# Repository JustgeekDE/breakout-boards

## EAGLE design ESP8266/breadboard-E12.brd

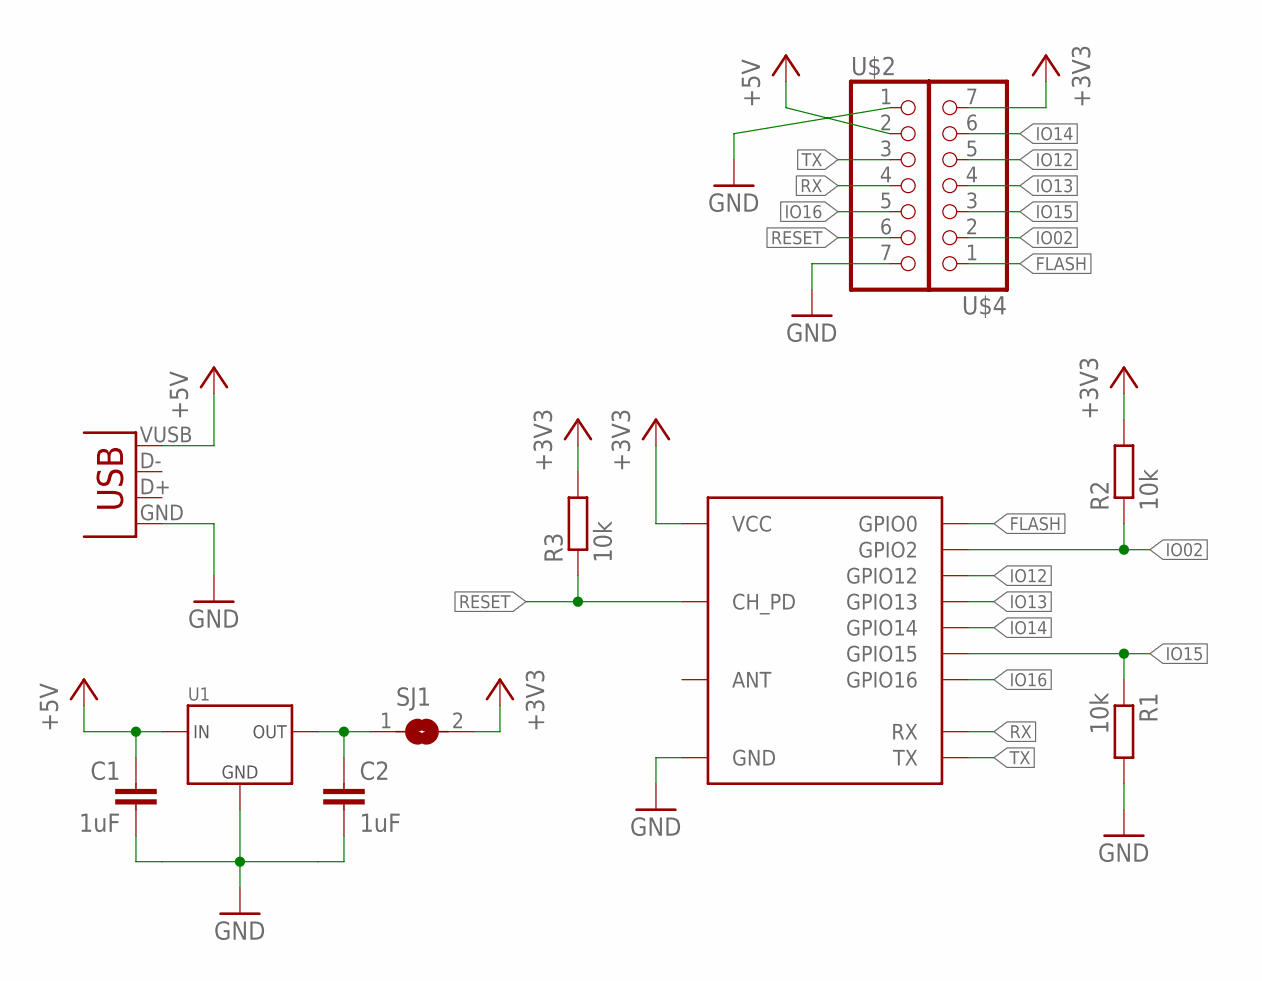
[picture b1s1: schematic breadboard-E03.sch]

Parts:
C1, C2: 1uF; C0805
CON1: USBMICRO-NO_CENTER; USB-MICRO-SMD-NO_CENTER
R1, R2, R3: 10k; R0603
SJ1: SJ
U1: REGULATOR-XC6206SOT23; SOT23
U$1: ESP8266-03; ESP8266-ESP-03
U$2, U$4: GENERIC-1X7; PINHEADER-100MIL-1X7

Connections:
+3V3: R2.2, R3.2, SJ1.2, U$1.P$8 (VCC), U$4.7
+5V: C1.1, CON1.VUSB (VBUS), U1.P$3 (IN), U$2.2
FLASH: U$1.P$14 (GPIO0), U$4.1
GND: C1.2, C2.2, CON1.GND, R1.2, U1.P$1 (GND), U$1.P$1 (GND), U$2.1, U$2.7
IO02: R2.1, U$1.P$13 (GPIO2), U$4.2
IO12: U$1.P$10 (GPIO12), U$4.5
IO13: U$1.P$11 (GPIO13), U$4.4
IO14: U$1.P$9 (GPIO14), U$4.6
IO15: R1.1, U$1.P$12 (GPIO15), U$4.3
IO16: U$1.P$5 (GPIO16), U$2.5
unnamed: C2.1, SJ1.1, U1.P$2 (OUT)
RESET: R3.1, U$1.P$6 (CH_PD), U$2.6
RX: U$1.P$4 (RX), U$2.4
TX: U$1.P$3 (TX), U$2.3

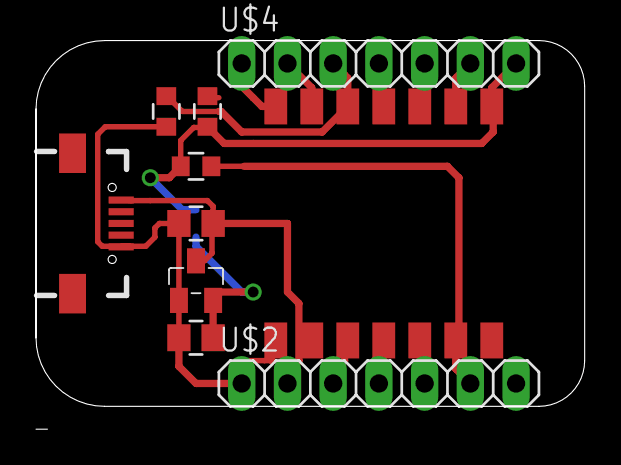
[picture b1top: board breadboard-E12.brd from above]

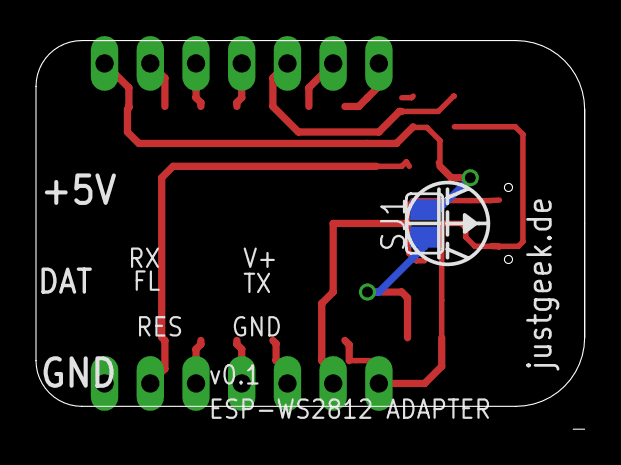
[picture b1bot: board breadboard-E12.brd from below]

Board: 2 copper layers, 30.5 x 21.6 mm, 12 parts (2 on the bottom side), 14 nets.

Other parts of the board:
U$3: LOGO-JUSTGEEK-XS

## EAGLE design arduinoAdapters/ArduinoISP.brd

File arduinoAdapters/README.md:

# Arduino ISP
A small adapter from the arduino header to the common AVR 6-pin programming header. Can be etched with basic home equipment.

Use a jumper wire to connect to the 5V rail on the other side of the Arduino, if necessary.

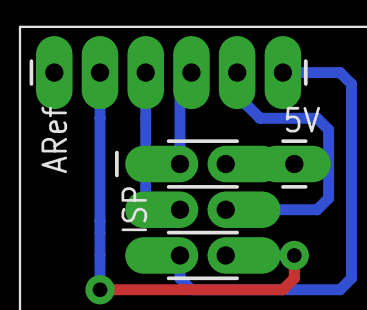
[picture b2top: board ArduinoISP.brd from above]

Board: 2 copper layers, 3 parts (0 on the bottom side), 6 nets.

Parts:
5V: M01PTH_LONGPAD; 1X01_LONGPAD
CON: 1X06_LONGPADS
ISP: AVR_SPI_PRG_6OFFSET_PADS; 2X3_OFFSET

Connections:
GND: CON.2, ISP.6
MISO: CON.4, ISP.1
MOSI: CON.5, ISP.4
RESET: CON.6, ISP.5
SCK: CON.3, ISP.3
VCC: 5V.1, ISP.2

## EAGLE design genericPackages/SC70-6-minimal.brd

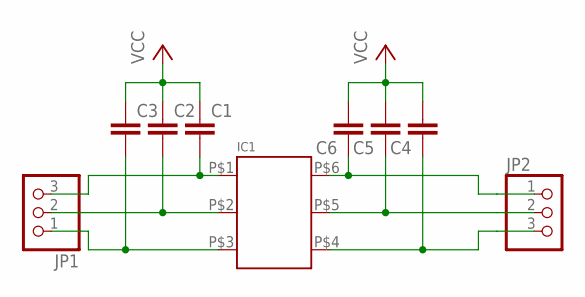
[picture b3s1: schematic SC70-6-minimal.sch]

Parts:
C1, C2, C3, C4, C5, C6: C-EUC0603; C0603
IC1: FOOTPRINT-6-PINSC70; SC-70/6
JP1, JP2: PINHD-1X3; 1X03

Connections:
1: C1.2, IC1.P$1 (1), JP1.3
2: C2.2, IC1.P$2 (2), JP1.2
3: C3.2, IC1.P$3 (3), JP1.1
4: C4.1, IC1.P$4 (4), JP2.3
5: C5.1, IC1.P$5 (5), JP2.2
6: C6.1, IC1.P$6 (6), JP2.1
VCC: C1.1, C2.1, C3.1, C4.2, C5.2, C6.2

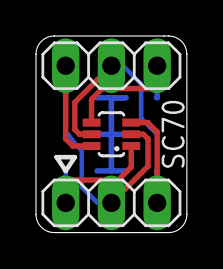
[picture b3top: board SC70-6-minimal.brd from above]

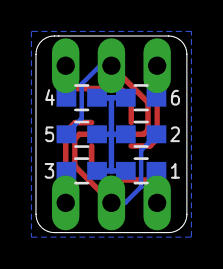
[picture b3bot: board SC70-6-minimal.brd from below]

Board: 2 copper layers, 8.4 x 10.9 mm, 9 parts (6 on the bottom side), 7 nets.

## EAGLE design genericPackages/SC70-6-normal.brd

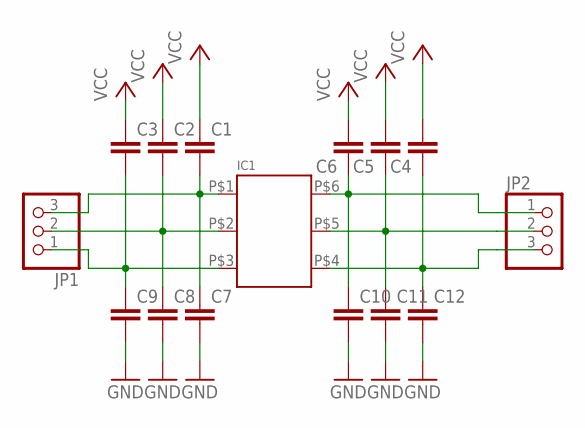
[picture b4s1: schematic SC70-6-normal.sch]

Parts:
C1, C2, C3, C4, C5, C6: C-EUC0805; C0805
C7, C8, C9, C10, C11, C12: C-EUC0603; C0603
IC1: FOOTPRINT-6-PINSC70; SC-70/6
JP1, JP2: PINHD-1X3; 1X03

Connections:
1: C1.2, C7.1, IC1.P$1 (1), JP1.3
2: C2.2, C8.1, IC1.P$2 (2), JP1.2
3: C3.2, C9.1, IC1.P$3 (3), JP1.1
4: C4.1, C12.1, IC1.P$4 (4), JP2.3
5: C5.1, C11.1, IC1.P$5 (5), JP2.2
6: C6.1, C10.1, IC1.P$6 (6), JP2.1
GND: C7.2, C8.2, C9.2, C10.2, C11.2, C12.2
VCC: C1.1, C2.1, C3.1, C4.2, C5.2, C6.2

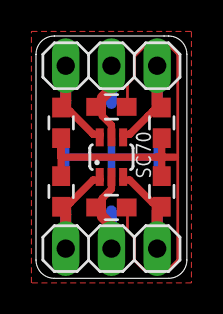
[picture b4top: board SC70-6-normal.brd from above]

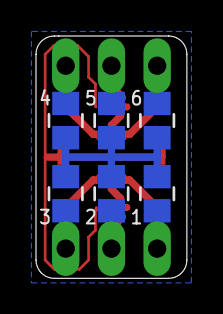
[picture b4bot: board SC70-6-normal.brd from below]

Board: 2 copper layers, 8.4 x 13.5 mm, 15 parts (6 on the bottom side), 8 nets.

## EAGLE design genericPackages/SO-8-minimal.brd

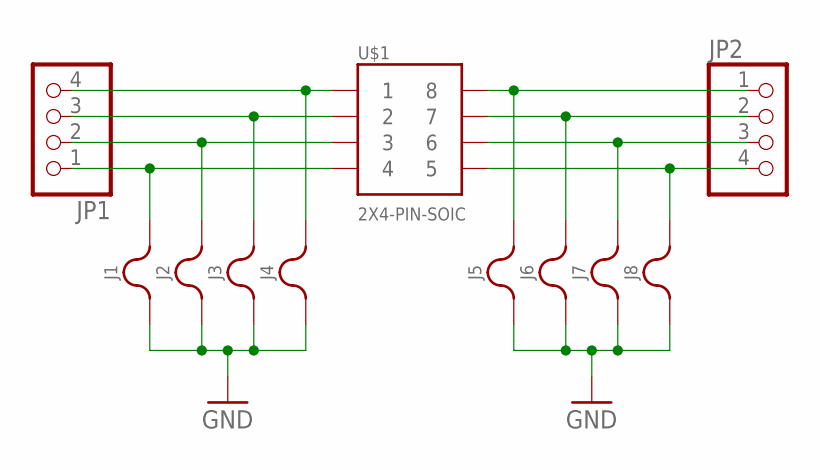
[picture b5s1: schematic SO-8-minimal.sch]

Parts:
J1, J2, J3, J4, J5, J6, J7, J8: JUMPER-0805; RCLJ-0805
JP1, JP2: PINHD-1X4; 1X04
U$1: 2X4-PIN-SOIC; SO8

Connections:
1: J4.2, JP1.4, U$1.P$1 (1)
2: J3.2, JP1.3, U$1.P$2 (2)
3: J2.2, JP1.2, U$1.P$3 (3)
4: J1.2, JP1.1, U$1.P$4 (4)
5: J8.2, JP2.4, U$1.P$5 (5)
6: J7.2, JP2.3, U$1.P$6 (6)
7: J6.2, JP2.2, U$1.P$7 (7)
8: J5.2, JP2.1, U$1.P$8 (8)
GND: J1.1, J2.1, J3.1, J4.1, J5.1, J6.1, J7.1, J8.1

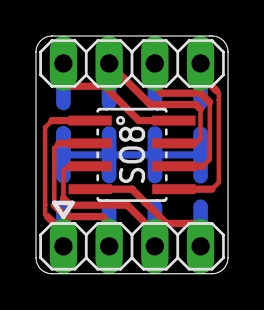
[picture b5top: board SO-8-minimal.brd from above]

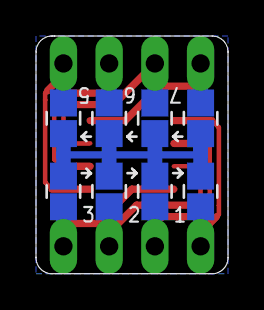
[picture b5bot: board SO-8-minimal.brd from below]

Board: 2 copper layers, 10.7 x 13.2 mm, 11 parts (8 on the bottom side), 9 nets.

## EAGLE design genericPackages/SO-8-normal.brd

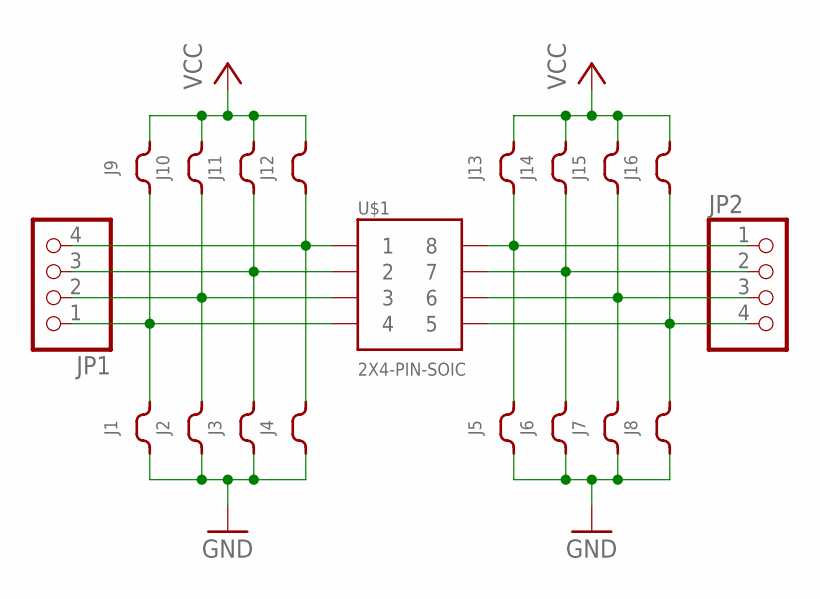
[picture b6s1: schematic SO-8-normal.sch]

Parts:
J1, J2, J3, J4, J5, J6, J7, J8: JUMPER-0805; RCLJ-0805
J9, J10, J11, J12, J13, J14, J15, J16: JUMPER-0603; RCLJ-0603
JP1, JP2: PINHD-1X4; 1X04
U$1: 2X4-PIN-SOIC; SO8

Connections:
1: J4.2, J12.1, JP1.4, U$1.P$1 (1)
2: J3.2, J11.1, JP1.3, U$1.P$2 (2)
3: J2.2, J10.1, JP1.2, U$1.P$3 (3)
4: J1.2, J9.1, JP1.1, U$1.P$4 (4)
5: J8.2, J16.1, JP2.4, U$1.P$5 (5)
6: J7.2, J15.1, JP2.3, U$1.P$6 (6)
7: J6.2, J14.1, JP2.2, U$1.P$7 (7)
8: J5.2, J13.1, JP2.1, U$1.P$8 (8)
GND: J1.1, J2.1, J3.1, J4.1, J5.1, J6.1, J7.1, J8.1
VCC: J9.2, J10.2, J11.2, J12.2, J13.2, J14.2, J15.2, J16.2

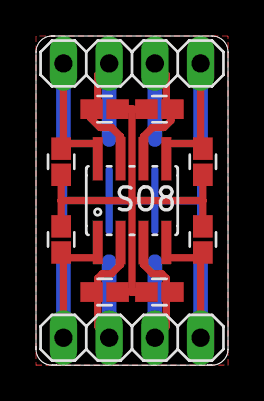
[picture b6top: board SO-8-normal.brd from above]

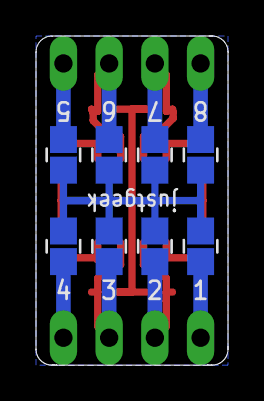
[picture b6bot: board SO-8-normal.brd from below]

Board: 2 copper layers, 10.7 x 18.3 mm, 19 parts (8 on the bottom side), 10 nets.
